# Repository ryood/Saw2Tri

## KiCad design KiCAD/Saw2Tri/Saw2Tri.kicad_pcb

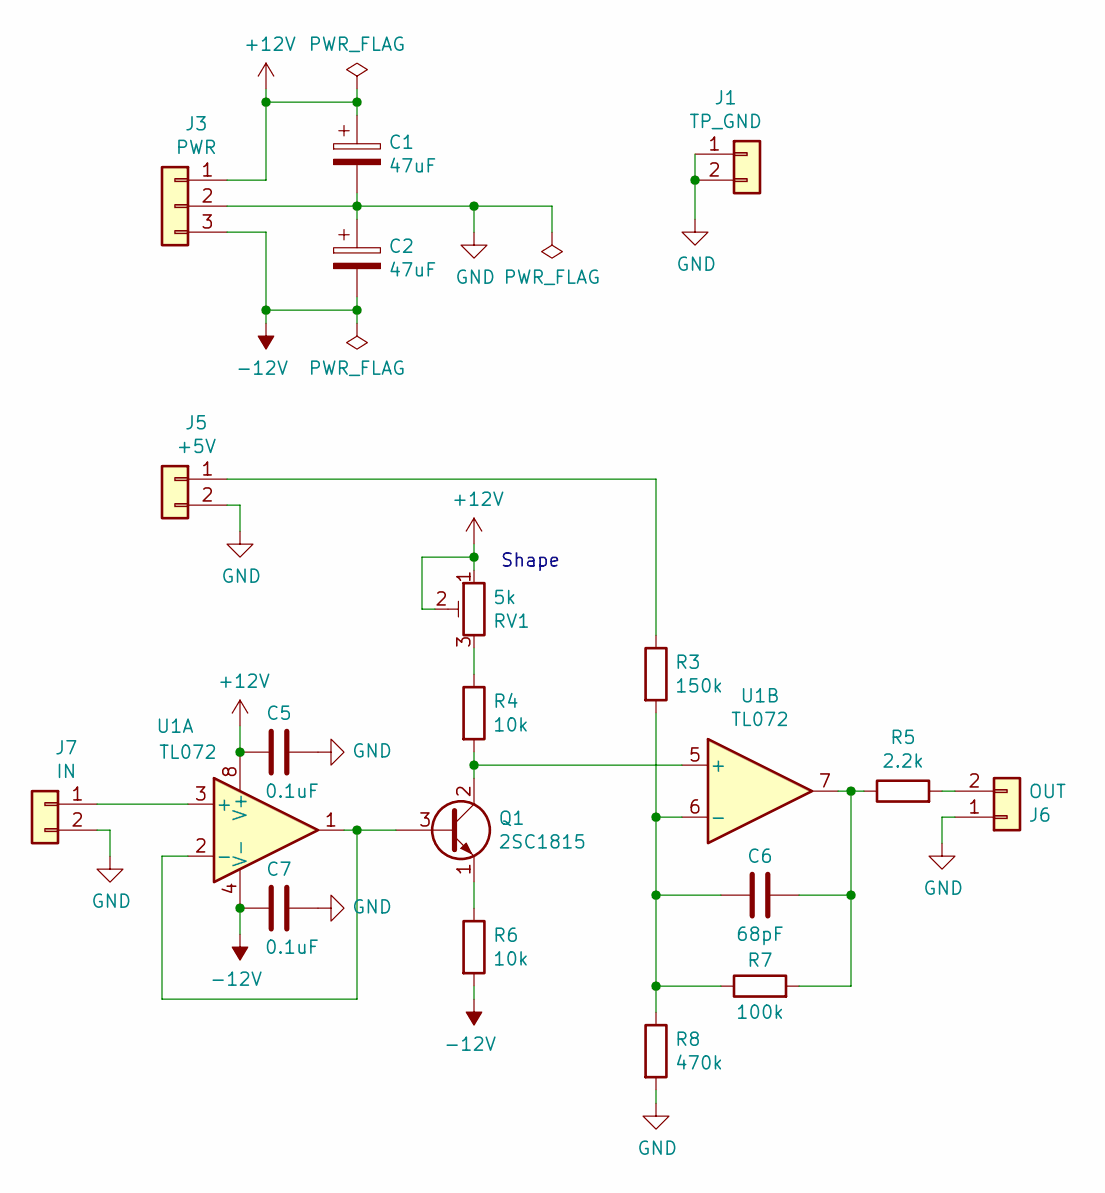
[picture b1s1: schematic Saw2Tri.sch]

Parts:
C1, C2: 47uF; CP_Radial_D5.0mm_P2.50mm
C5, C7: 0.1uF; C_Disc_D3.0mm_W1.6mm_P2.50mm
C6: 68pF; C_Disc_D5.0mm_W2.5mm_P5.00mm
J1: TP_GND; PinHeader_1x02_P2.54mm_Vertical
J3: PWR; JST_XH_S3B-XH-A_1x03_P2.50mm_Horizontal
J5: +5V; JST_XH_S2B-XH-A_1x02_P2.50mm_Horizontal
J6: OUT; JST_XH_B2B-XH-A_1x02_P2.50mm_Vertical
J7: IN; JST_XH_S2B-XH-A_1x02_P2.50mm_Horizontal
Q1: 2SC1815; TO-92_Inline_Wide
R3: 150k; R_Axial_DIN0207_L6.3mm_D2.5mm_P7.62mm_Horizontal
R4, R6: 10k; R_Axial_DIN0207_L6.3mm_D2.5mm_P7.62mm_Horizontal
R5: 2.2k; R_Axial_DIN0207_L6.3mm_D2.5mm_P7.62mm_Horizontal
R7: 100k; R_Axial_DIN0207_L6.3mm_D2.5mm_P7.62mm_Horizontal
R8: 470k; R_Axial_DIN0207_L6.3mm_D2.5mm_P7.62mm_Horizontal
RV1: 5k; JST_XH_B3B-XH-A_1x03_P2.50mm_Vertical
U1: TL072; DIP-8_W7.62mm_Socket

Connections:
+12V: C1.1, C5.2, J3.1, RV1.1, RV1.2, U1.8 (V+)
-12V: C2.2, C7.2, J3.3, R6.2, U1.4 (V-)
GND: C1.2, C2.1, C5.1, C7.1, J1.1, J1.2, J3.2, J5.2, J6.1, J7.2, R8.2
unnamed: C6.1, R5.1, R7.2, U1.7
unnamed: C6.2, R3.2, R7.1, R8.1, U1.6 (-)
unnamed: J5.1, R3.1
unnamed: J6.2, R5.2
unnamed: J7.1, U1.3 (+)
unnamed: Q1.1 (E), R6.1
unnamed: Q1.2 (C), R4.2, U1.5 (+)
unnamed: Q1.3 (B), U1.1, U1.2 (-)
unnamed: R4.1, RV1.3

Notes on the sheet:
Shape

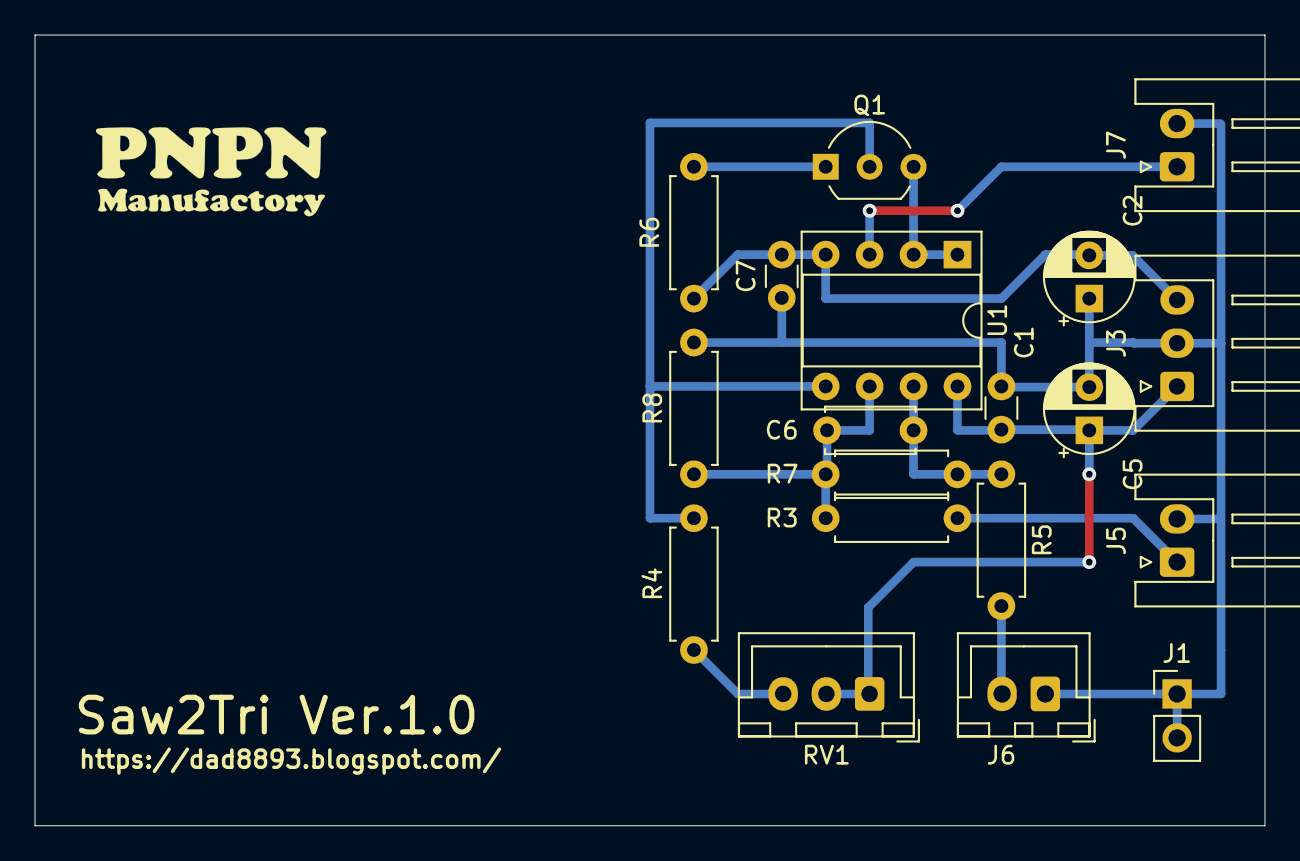
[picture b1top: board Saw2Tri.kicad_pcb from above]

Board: 2 copper layers, 71.1 x 45.7 mm, 19 parts (0 on the bottom side), 12 nets.

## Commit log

2021-04-22 Board design
